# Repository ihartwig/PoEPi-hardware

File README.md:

Raspberry Pi Zero PoE - PoEPi
=============================

This repository houses multiple designs for a PoE hat for RPi Zero that combines a 802.3af compliant controller with a 10Mbps ethernet controller/phy to provide power and connectivity over the same cable. The board shape matches RPi Zero, but this board should work on RPi 1/2/3 with 40-pin GPIO and the right headers. Footprints for the RPi Hat EEPROM are present but untested.

</img>

## Features
* 5V 12.95W 802.3af-compliant PoE with LTC4267
* 10Mbps ethernet using ENC28J60 (includes Raspbian driver support)

## Variations

* **passive-poe-only-top-smt**: Schematic only (layout abandoned) for an FRC Passive PoE (4-18V) variant using a TPS63070 buck-boost regulator
  * Ported sch, pcb, and libs to KiCAD 7.0.2
  * New project at https://github.com/ihartwig/ether-friends/tree/main/pizero-papoe
* **poe-only-top-smt**: Rev 2 with only PoE parts and all parts on top for easy automated assembly.
  * [Order bare pcbs from Dirty PCB](http://dirtypcbs.com/view.php?share=26685&accesskey=).
  * Known issues:
    * J1 TPIN+/- pair is on the wrong pins - no link up
    * PoE negotiation does not complete
* **servo-controller**: Rev 1 with buffered output to drive 3 servos.
* **speaker-amplifier**: Rev 1 with an amplifier for the RPi's PWM audio output.
* **ws2812-controller**: Rev 1 with a connector for NeoPixels.

## Raspberry Pi Zero - PoEPi

The Raspberry Pi Zero is a low power and low footprint Raspberry Pi. It gives people an opportunity to move towards compact connected devices
while moving away from being a just a small computer. PiPoE adds a new way of connecting the Raspberry Pi Zero with the world in a very efficient
manner. Power over Ethernet is a way if injecting power into an Ethernet cable without interfering with the data. What it gives you is a high 
reliability way of powering and communicating with the Raspberry Pi. The design of PoEPi is open source under the CERN OHL V1.2 and can be easily
adapted to your own custom designs. 

For more information check out the Wiki on github

### Basic Hardware usage

1. Setup your Raspberry Pi with a monitor and enable SSH with raspi-config
2. Plug Ethernet cable into a PoE switch or add a PoE injector somehwhere in you Ethernet line
3. Connect the PoEPi to the Raspberry Pi
4. Plug in the "injected" Ethernet cable
5. The Pi Zero should be powered and you then SSH into the Pi

For information on the particular PoEPi modules and how to control them please see the wiki on the github page

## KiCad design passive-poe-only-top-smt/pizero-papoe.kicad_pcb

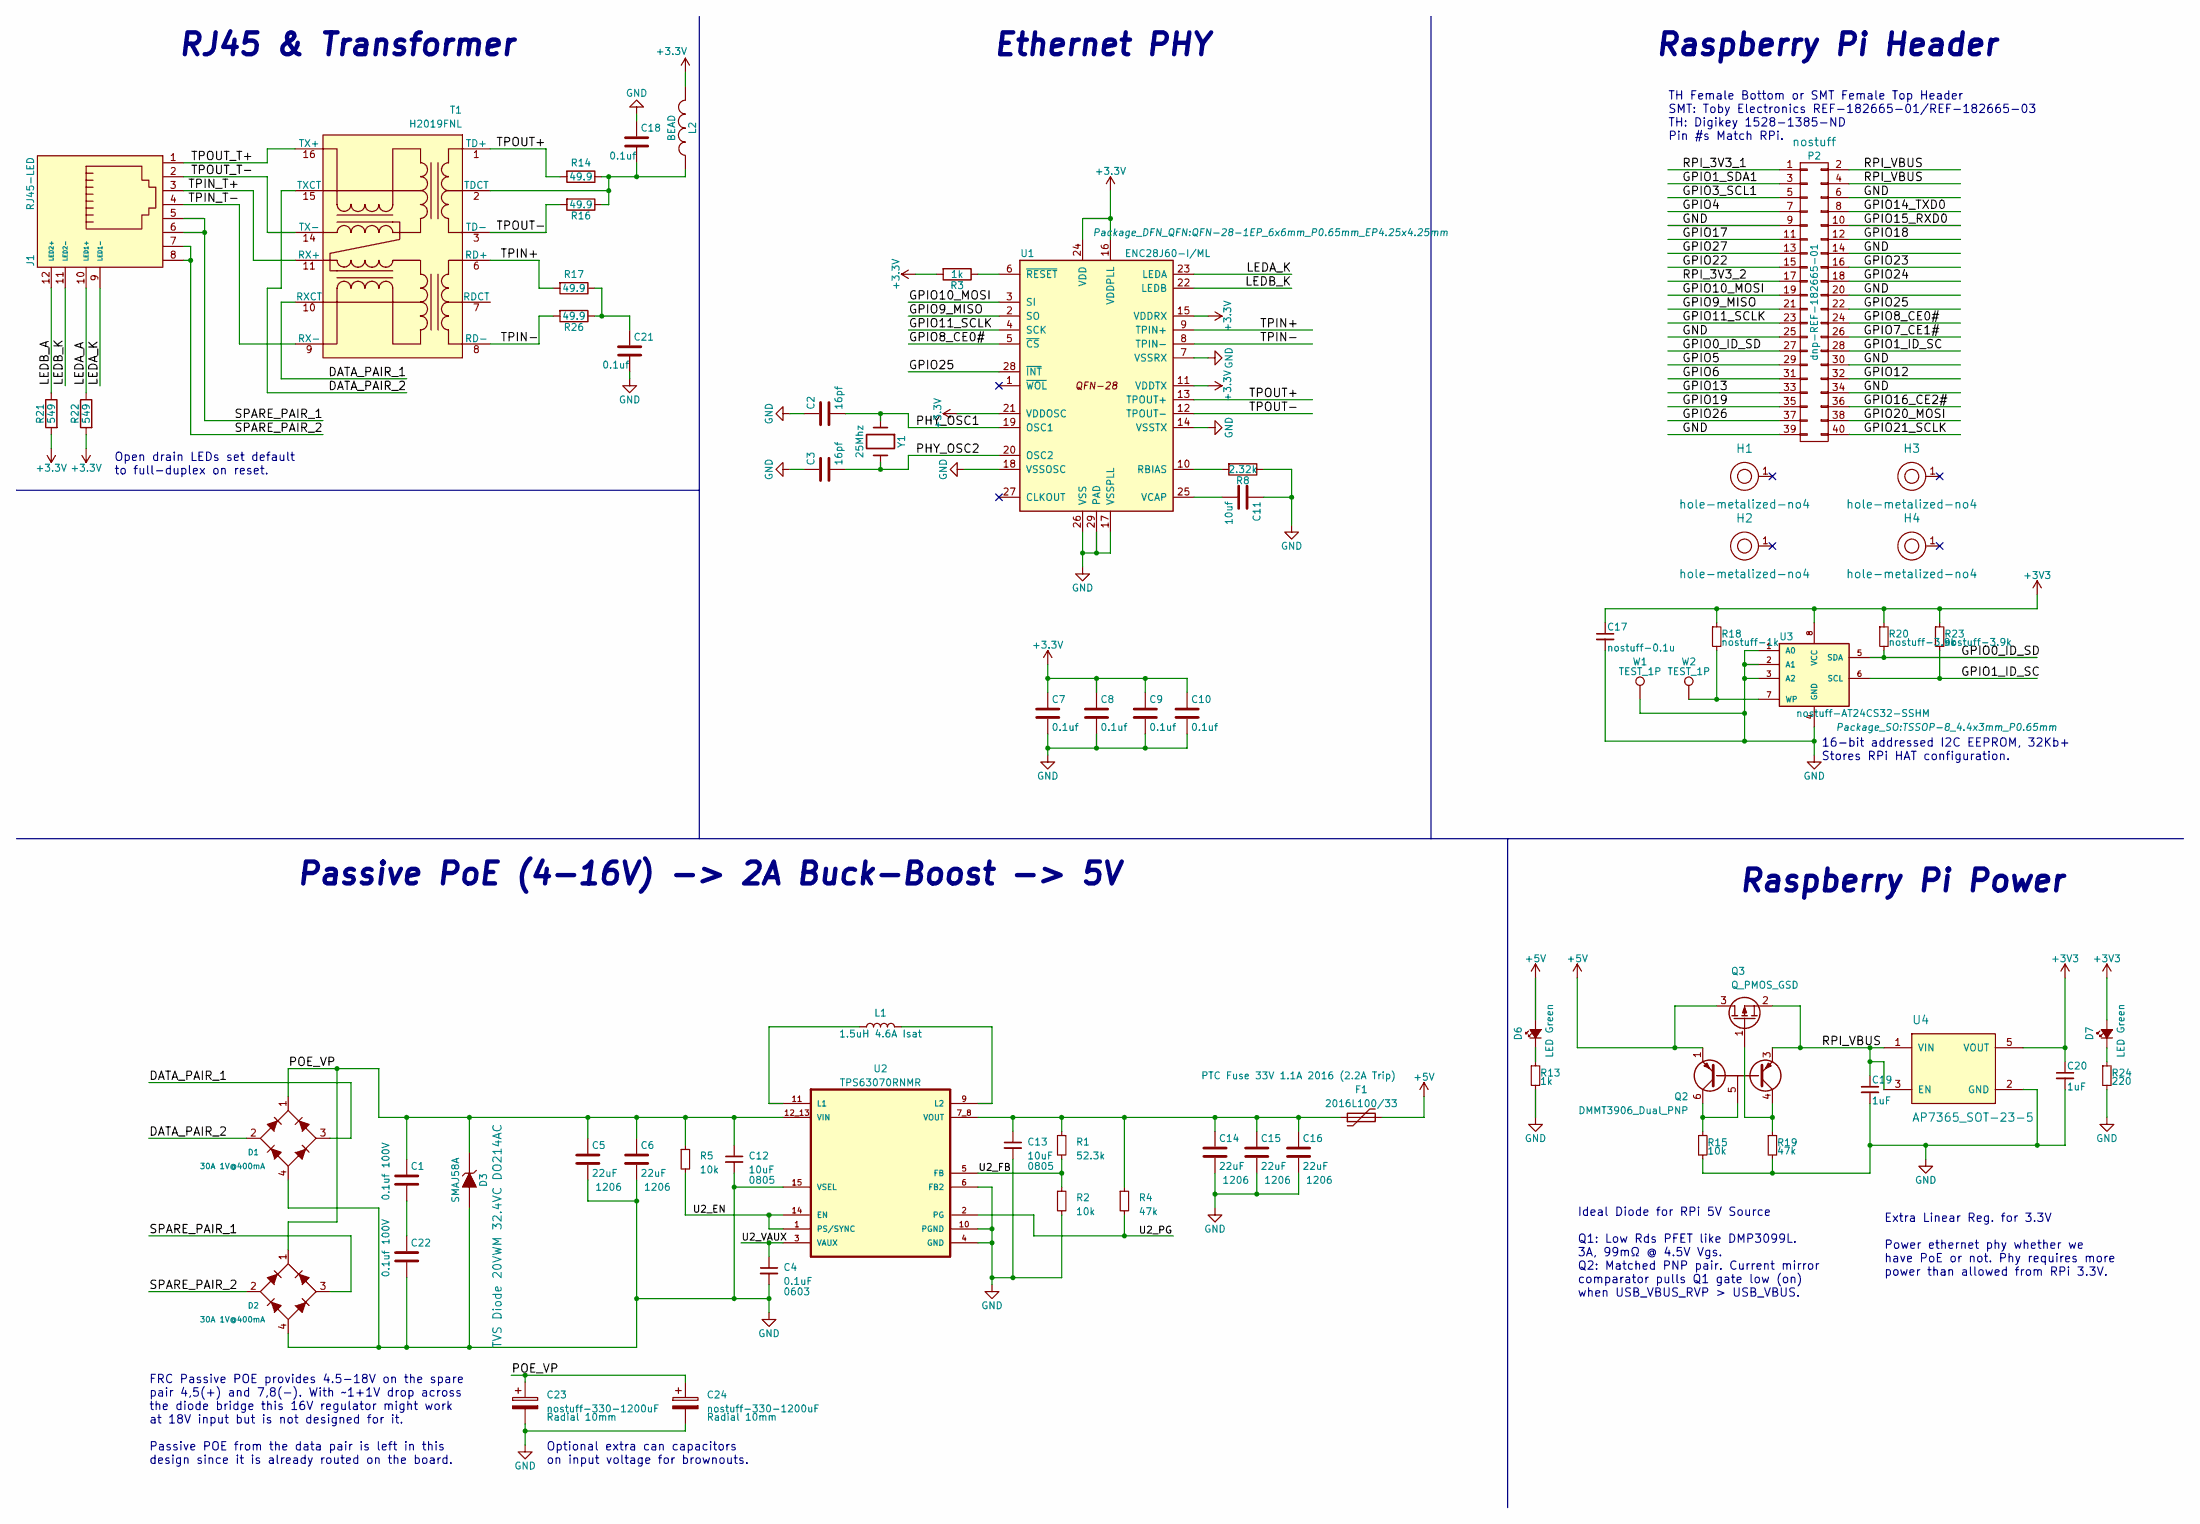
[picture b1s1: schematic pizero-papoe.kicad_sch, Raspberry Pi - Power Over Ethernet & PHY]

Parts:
C1, C22: 0.1uf 100V; C_0603_1608Metric; Mfg Part No CL10B104KC8NNNC; Digikey Part No 1276-6807-1-ND
C2, C3: 16pf; C_0603_1608Metric
C4: 0.1uF; C_0603_1608Metric; Mfg Part No CC0603KRX7R7BB104; LCSC C108079
C5: 22uF; C_1206_3216Metric; Mfg Part No CC1206KKX5R8BB226; LCSC C2178233
C6, C14, C15, C16: 22uF; C_1206_3216Metric
C7, C8, C9, C10, C18, C21: 0.1uf; C_0603_1608Metric
C11: 10uf; C_1206_3216Metric
C12: 10uF; C_0805_2012Metric; Mfg Part No GRT21BC71E106KE13L; LCSC C882505
C13: 10uF; C_0805_2012Metric
C17: nostuff-0.1u; C_0603_1608Metric
C19, C20: 1uF; C_0603_1608Metric
C23, C24: nostuff-330-1200uF; CP_Radial_D10.0mm_P5.00mm; Mfg Part No RNL1E122MDSASQ
D1: 30A 1V@400mA; MBS; Mfg Part No HD01-T; Digikey Part No HD01DICT-ND
D2: 30A 1V@400mA; MBS
D3: SMAJ58A; D_SMA; Mfg Part No SMAJ20A; LCSC C148209
D6, D7: LED Green; LED_0603_1608Metric; Mfg Part No LTST-C190GKT; Digikey Part No 160-1183-1-ND
F1: 2016L100/33; Mfg Part No 2016L100/33DR; LCSC C207077
H1, H2, H3, H4: hole-metalized-no4; hole-m3
J1: RJ45-LED; rj45-tyco-2-406549-7; Mfg Part No RJHSE-5081; Digikey Part No RJHSE-5081-ND
L1: 1.5uH 4.6A Isat; L_Sunlord_SWPA4030S; Mfg Part No XFL4020-152ME; JLCPCB Part # LCSC
L2: BEAD; R_0603_1608Metric; Mfg Part No BK1608HS102-T; Digikey Part No 587-1867-1-ND
P2: dnp-REF-182665-01; Pin_Header_Straight_TH-SMT-NoPaste_2x20
Q2: DMMT3906_Dual_PNP; SOT-23-6; Mfg Part No DMMT3906-7-F; Digikey Part No DMMT3906-7-FDICT-ND
Q3: Q_PMOS_GSD; SOT-23; Mfg Part No DMP3099L-7; Digikey Part No DMP3099L-7DICT-ND
R1: 52.3k; R_0603_1608Metric
R2, R5, R15: 10k; R_0603_1608Metric
R3, R13: 1k; R_0603_1608Metric
R4, R19: 47k; R_0603_1608Metric
R8: 2.32k; R_0603_1608Metric
R14, R16, R17, R26: 49.9; R_0603_1608Metric
R18: nostuff-1k; R_0603_1608Metric
R20, R23: nostuff-3.9k; R_0603_1608Metric
R21, R22: 549; R_0603_1608Metric
R24: 220; R_0603_1608Metric
T1: H2019FNL; Transformer_Pulse_H2019FNL; Mfg Part No 749013011A; Digikey Part No 732-7063-1-ND
U1: ENC28J60-I/ML; QFN-28-1EP_6x6mm_P0.65mm_EP4.25x4.25mm; Mfg Part No ENC28J60-I/ML; Digikey Part No ENC28J60-I/ML-ND
U2: TPS63070RNMR; VREG_TPS63070RNMR; Mfg Part No TPS63070RNMR; LCSC C109322
U3: nostuff-AT24CS32-SSHM; TSSOP-8_4.4x3mm_P0.65mm
U4: AP7365_SOT-23-5; SOT-23-5; Mfg Part No AP7365-33WG-7; Digikey Part No AP7365-33WG-7DICT-ND
W1, W2: TEST_1P; TestPoint_Pad_D1.0mm
Y1: 25Mhz; Crystal_SMD_5032-2Pin_5.0x3.2mm; Mouser Part No. 774-445I23D25M00000

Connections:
+5V: D6.2 (A), F1.2, Q2.1 (E1), Q3.3 (D)
/DATA_PAIR_1: D1.3 (~2), T1.10 (RXCT)
/DATA_PAIR_2: D1.2 (~1), T1.15 (TXCT)
/GPIO0_ID_SD: P2.27, R20.2, U3.5 (SDA)
/GPIO1_ID_SC: P2.28, R23.2, U3.6 (SCL)
/GPIO1_SDA1: P2.3
/GPIO3_SCL1: P2.5
/GPIO4: P2.7
/GPIO5: P2.29
/GPIO6: P2.31
/GPIO7_CE1#: P2.26
/GPIO8_CE0#: P2.24, U1.5 (~CS)
/GPIO9_MISO: P2.21, U1.2 (SO)
/GPIO10_MOSI: P2.19, U1.3 (SI)
/GPIO11_SCLK: P2.23, U1.4 (SCK)
/GPIO12: P2.32
/GPIO13: P2.33
/GPIO14_TXD0: P2.8
/GPIO15_RXD0: P2.10
/GPIO16_CE2#: P2.36
/GPIO17: P2.11
/GPIO18: P2.12
/GPIO19: P2.35
/GPIO20_MOSI: P2.38
/GPIO21_SCLK: P2.40
/GPIO22: P2.15
/GPIO23: P2.16
/GPIO24: P2.18
/GPIO25: P2.22, U1.28 (~INT)
/GPIO26: P2.37
/GPIO27: P2.13
/LEDA_A: J1.10 (LED1+), R22.1
/LEDA_K: J1.9 (LED1-), U1.23 (LEDA)
/LEDB_A: J1.12 (LED2+), R21.1
/LEDB_K: J1.11 (LED2-), U1.22 (LEDB)
/PHY_OSC1: C2.2, U1.19 (OSC1), Y1.1
/PHY_OSC2: C3.2, U1.20 (OSC2), Y1.2
/POE_VP: C1.1, C5.1, C6.1, C12.1, C23.1, C24.1, D1.1 (V+), D2.1 (V+), D3.1 (K), R5.1, U2.12_13 (VIN)
/RPI_3V3_1: P2.1
/RPI_3V3_2: P2.17
/RPI_VBUS: C19.1, P2.2, P2.4, Q2.3 (E2), Q3.2 (S), U4.1 (VIN), U4.3 (EN)
/SPARE_PAIR_1: D2.3 (~2), J1.5, J1.6
/SPARE_PAIR_2: D2.2 (~1), J1.7, J1.8
/TPIN+: R17.2, T1.6 (RD+), U1.9 (TPIN+)
/TPIN-: R26.2, T1.8 (RD-), U1.8 (TPIN-)
/TPIN_T+: J1.3, T1.11 (RX+)
/TPIN_T-: J1.4, T1.9 (RX-)
/TPOUT+: R14.2, T1.1 (TD+), U1.13 (TPOUT+)
/TPOUT-: R16.2, T1.3 (TD-), U1.12 (TPOUT-)
/TPOUT_T+: J1.1, T1.16 (TX+)
/TPOUT_T-: J1.2, T1.14 (TX-)
/U2_EN: R5.2, U2.1 (PS/SYNC), U2.14 (EN)
/U2_FB: R1.2, R2.1, U2.5 (FB)
/U2_PG: R4.2, U2.2 (PG)
/U2_VAUX: C4.1, U2.3 (VAUX)
GND: C2.1, C3.1, C4.2, C5.2, C6.2, C7.2, C8.2, C9.2, C10.2, C11.1, C12.2, C13.2, C14.2, C15.2, C16.2, C17.2, C18.1, C19.2, C20.2, C21.2, C22.2, C23.2, C24.2, D1.4 (V-), D2.4 (V-), D3.2 (A), P2.6, P2.9, P2.14, P2.20, P2.25, P2.30, P2.34, P2.39, R2.2, R8.1, R13.2, R15.2, R19.2, R24.2, U1.7 (VSSRX), U1.14 (VSSTX), U1.17 (VSSPLL), U1.18 (VSSOSC), U1.26 (VSS), U1.29 (PAD), U2.4 (GND), U2.6 (FB2), U2.10 (PGND), U2.15 (VSEL), U3.1 (A0), U3.2 (A1), U3.3 (A2), U3.4 (GND), U4.2 (GND), W1.1
unnamed: C1.2, C22.1
unnamed: C21.1, R17.1, R26.1
unnamed: D6.1 (K), R13.1
unnamed: D7.1 (K), R24.1
unnamed: Q2.5 (B), Q2.6 (C1), R15.1
unnamed: Q2.4 (C2), Q3.1 (G), R19.1
unnamed: C18.2, L2.1, R14.1, R16.1, T1.2 (TDCT)
unnamed: R8.2, U1.10 (RBIAS)
unnamed: C11.2, U1.25 (VCAP)
unnamed: R3.1, U1.6 (~RESET)
unnamed: L1.1, U2.11 (L1)
unnamed: L1.2, U2.9 (L2)
unnamed: C13.1, C14.1, C15.1, C16.1, F1.1, R1.1, R4.1, U2.7_8 (VOUT)
unnamed: R18.2, U3.7 (WP), W2.1

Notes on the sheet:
TH Female Bottom or SMT Female Top Header SMT: Toby Electronics REF-182665-01/REF-182665-03 TH: Digikey 1528-1385-ND Pin #s Match RPi.
Raspberry Pi Header
16-bit addressed I2C EEPROM, 32Kb+ Stores RPi HAT configuration.
Passive PoE (4-16V) -> 2A Buck-Boost -> 5V
Raspberry Pi Power
Ideal Diode for RPi 5V Source Q1: Low Rds PFET like DMP3099L. 3A, 99mΩ @ 4.5V Vgs. Q2: Matched PNP pair. Current mirror comparator pulls Q1 gate low (on) when USB_VBUS_RVP > USB_VBUS.
Extra Linear Reg. for 3.3V Power ethernet phy whether we have PoE or not. Phy requires more power than allowed from RPi 3.3V.
Open drain LEDs set default to full-duplex on reset.
FRC Passive POE provides 4.5-18V on the spare pair 4,5(+) and 7,8(-). With ~1+1V drop across the diode bridge this 16V regulator might work at 18V input but is not designed for it. Passive POE from the data pair is left in this design since it is already routed on the board.
RJ45 & Transformer
Optional extra can capacitors on input voltage for brownouts.
Ethernet PHY

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
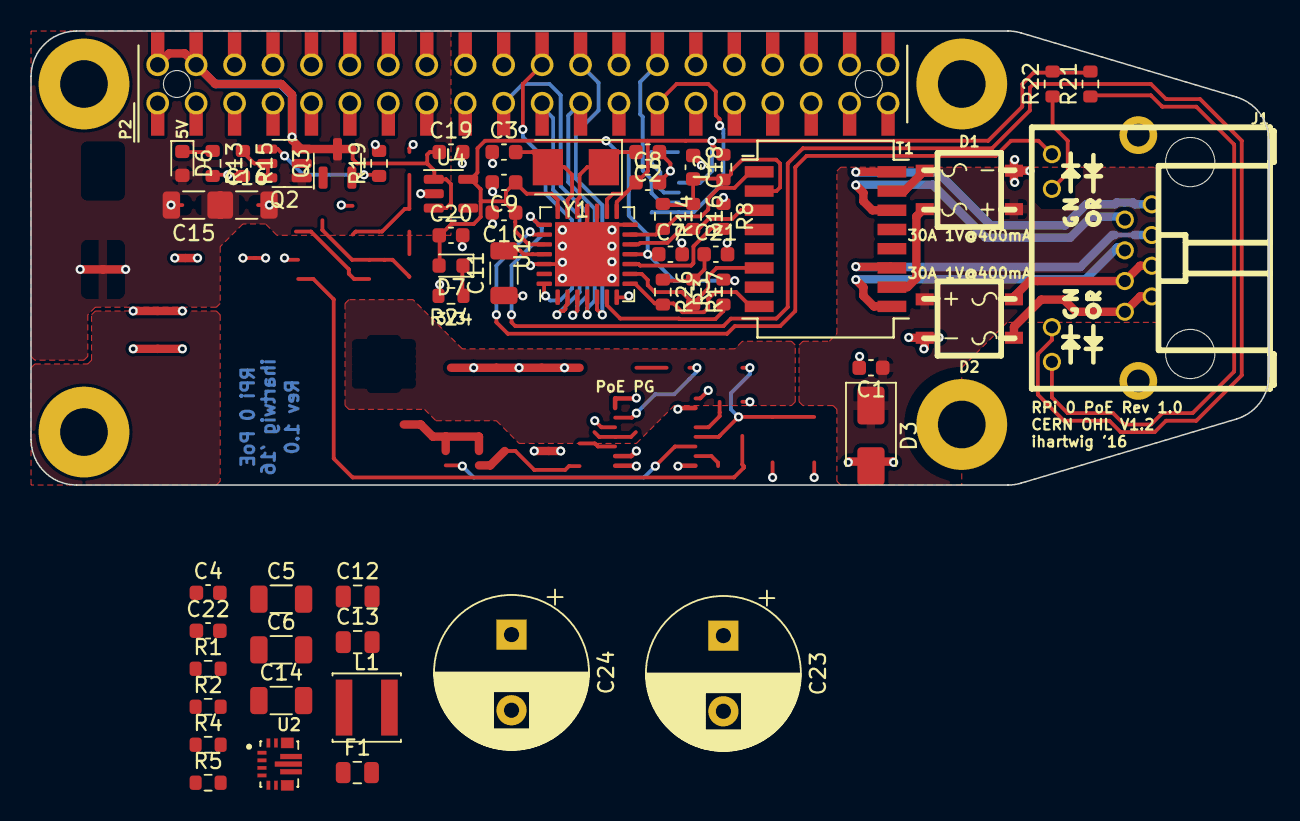
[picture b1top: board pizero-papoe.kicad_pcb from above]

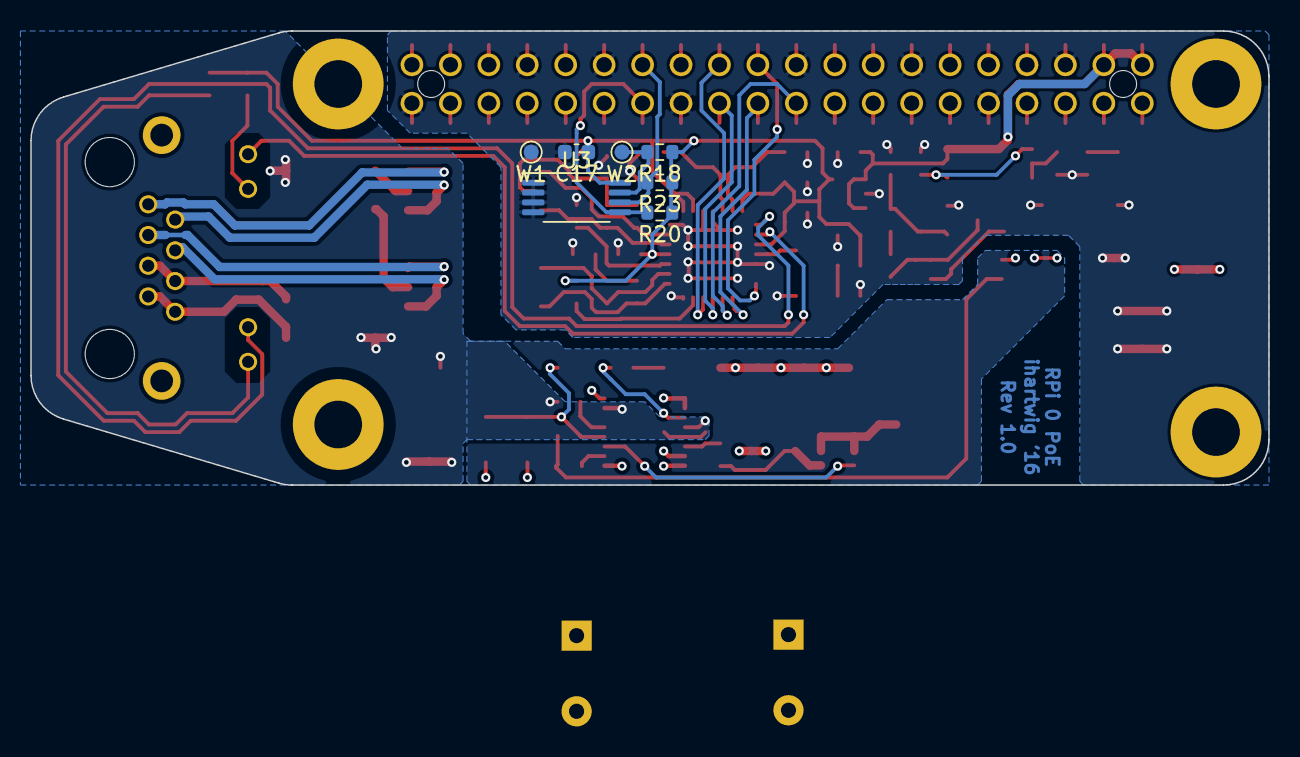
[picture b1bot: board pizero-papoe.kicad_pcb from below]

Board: 2 copper layers, 81.8 x 30.0 mm, 67 parts (7 on the bottom side), 48 nets.

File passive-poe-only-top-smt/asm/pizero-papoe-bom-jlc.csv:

Comment,Designator,Footprint,LCSC
"0.1uf 100V","C1","Capacitor_SMD:C_0603_1608Metric",""
"10uf","C11","Capacitor_SMD:C_1206_3216Metric",""
"470uF","C12","Capacitor_SMD:CP_Elec_8x10",""
"0.1uF","C15,C16","Capacitor_SMD:C_0603_1608Metric",""
"nostuff-0.1u","C17","Capacitor_SMD:C_0603_1608Metric",""
"1uF","C19,C20","Capacitor_SMD:C_0603_1608Metric",""
"16pf","C2,C3","Capacitor_SMD:C_0603_1608Metric",""
"0.1uf","C7,C8,C9,C10,C18,C21","Capacitor_SMD:C_0603_1608Metric",""
"BRIDGE","D1,D2","pizero-poe-special:MBS","C52151"
"SMAJ58A","D3","Diode_SMD:D_SMA",""
"LED Green","D6,D7","LED_SMD:LED_0603_1608Metric",""
"hole-metalized-no4","H1,H2,H3,H4","pizero-poe-special:hole-m3",""
"RJ45-LED","J1","pizero-poe-special:rj45-tyco-2-406549-7",""
"1.5uH 4.6A Isat","L1","",""
"BEAD","L2","Resistor_SMD:R_0603_1608Metric",""
"dnp-REF-182665-01","P2","pizero-poe-special:Pin_Header_Straight_TH-SMT-NoPaste_2x20",""
"DMMT3906_Dual_PNP","Q2","Package_TO_SOT_SMD:SOT-23-6","C526572"
"Q_PMOS_GSD","Q3","Package_TO_SOT_SMD:SOT-23","C155244"
"R_Small","R1,R2,R4,R5","",""
"49.9","R14,R16,R17,R26","Resistor_SMD:R_0603_1608Metric",""
"10k","R15","Resistor_SMD:R_0603_1608Metric",""
"nostuff-1k","R18","Resistor_SMD:R_0603_1608Metric",""
"47k","R19","Resistor_SMD:R_0603_1608Metric",""
"nostuff-3.9k","R20,R23","Resistor_SMD:R_0603_1608Metric",""
"549","R21,R22","Resistor_SMD:R_0603_1608Metric",""
"220","R24","Resistor_SMD:R_0603_1608Metric",""
"1k","R3,R13","Resistor_SMD:R_0603_1608Metric",""
"2.32k","R8","Resistor_SMD:R_0603_1608Metric",""
"H2019FNL","T1","pizero-poe-special:Transformer_Pulse_H2019FNL","C7193798"
"ENC28J60-I/ML","U1","Package_DFN_QFN:QFN-28-1EP_6x6mm_P0.65mm_EP4.25x4.25mm","C629417"
"TPS63070RNMR","U2","TPS63070RNMR:VREG_TPS63070RNMR","C109322"
"nostuff-AT24CS32-SSHM","U3","Package_SO:TSSOP-8_4.4x3mm_P0.65mm",""
"AP7365_SOT-23-5","U4","Package_TO_SOT_SMD:SOT-23-5","C150742"
"TEST_1P","W1,W2","TestPoint:TestPoint_Pad_D1.0mm",""
"25Mhz","Y1","Crystal:Crystal_SMD_5032-2Pin_5.0x3.2mm",""

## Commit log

2016-09-15 copy ws2812-controller as base for poe-only-top-smt variant
2016-09-25 use rpi interface from ihartwig/raspberrypi-debugger and footprints from kicad 4+
2016-09-27 refresh parts on pcb and separate functional groups
2016-10-01 floorplan, named nets, design rules set
2016-10-05 complete routing for poe and ethernet
    * isolate to ~500Vac with .75-.8mm gaps between high and low voltage copper
    * remove extra 2x13 compatibility holes from pizero_poe_special:Pin_Header_Straight_TH-SMT-NoPaste_2x20, Pin_Header_Straight_TH-SMT_2x20 footprints
    * add insert attribute to pizero_poe_special:Crystal_Grounded_3.2x2.5, MBS, Pin_Header_Straight_TH-SMT_2x20, sod123, sod323, sod523 footprints.
    * change rpi hat eeprom power from RPI_3V3_2 to +3V3
    * calculate trace geometry for ethenet impedance control
2016-10-06 add datasheets, change eth magnetics, clean up silkscreen
2016-10-09 add part info to schematic for BOM. TODO: UPDATE LAYOUT
2016-10-10 fix layout for larger cap, isolation, solder mask
    * larger footprint for 470uF cap and adjust power and phy to fit
    * fix 3d model of rpi header for 20 pins
    * add soldermask expansion
    * allow soldermask tenting on ethernet phy ep
    * add gerbers
2018-07-22 update readme, bom, gerbers
2024-12-02 add passive-poe-only-top-smt variant schematic
2024-12-10 add schematic pcb and abandonment note

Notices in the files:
passive-poe-only-top-smt/pizero-papoe.kicad_pcb:
License: CERN OHL V1.2
